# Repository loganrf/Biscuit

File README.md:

# Biscuit
A board for prototyping basic RF circuits (filters etc).

Current design is only good to 1.8GHz. Work is underway to improve the end launch for better performance above that frequency.

Note the 4 extra SMA connectors on the edges. These can be enabled by using a knife to cut the center pad from the surrounding ground plane.

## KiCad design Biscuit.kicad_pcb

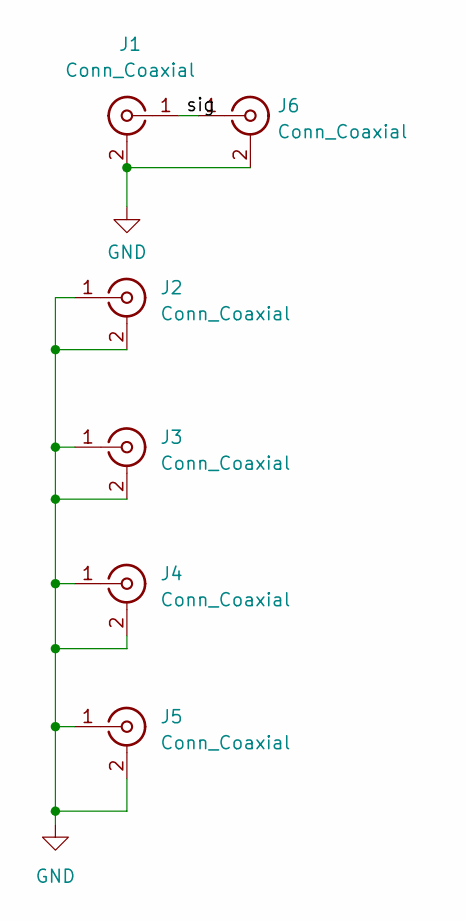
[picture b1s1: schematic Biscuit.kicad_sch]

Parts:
J1, J2, J3, J4, J5, J6: Conn_Coaxial; SMA_Amphenol_132289_EdgeMount

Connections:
/sig: J1.1 (In), J6.1 (In)
GND: J1.2 (Ext), J2.1 (In), J2.2 (Ext), J3.1 (In), J3.2 (Ext), J4.1 (In), J4.2 (Ext), J5.1 (In), J5.2 (Ext), J6.2 (Ext)

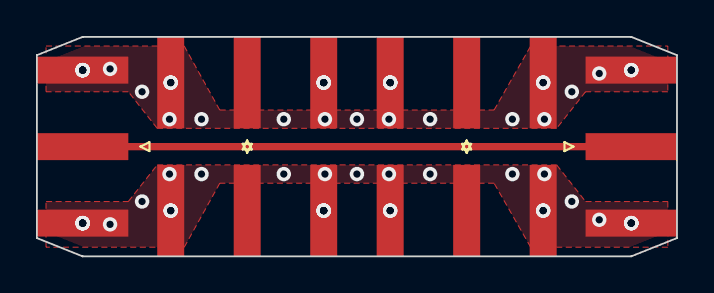
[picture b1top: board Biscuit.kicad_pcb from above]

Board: 4 copper layers, 35.6 x 12.2 mm, 6 parts (0 on the bottom side), 2 nets.

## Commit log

2022-02-14 Initial Commit at 004.BX
2022-02-14 Create LICENSE
